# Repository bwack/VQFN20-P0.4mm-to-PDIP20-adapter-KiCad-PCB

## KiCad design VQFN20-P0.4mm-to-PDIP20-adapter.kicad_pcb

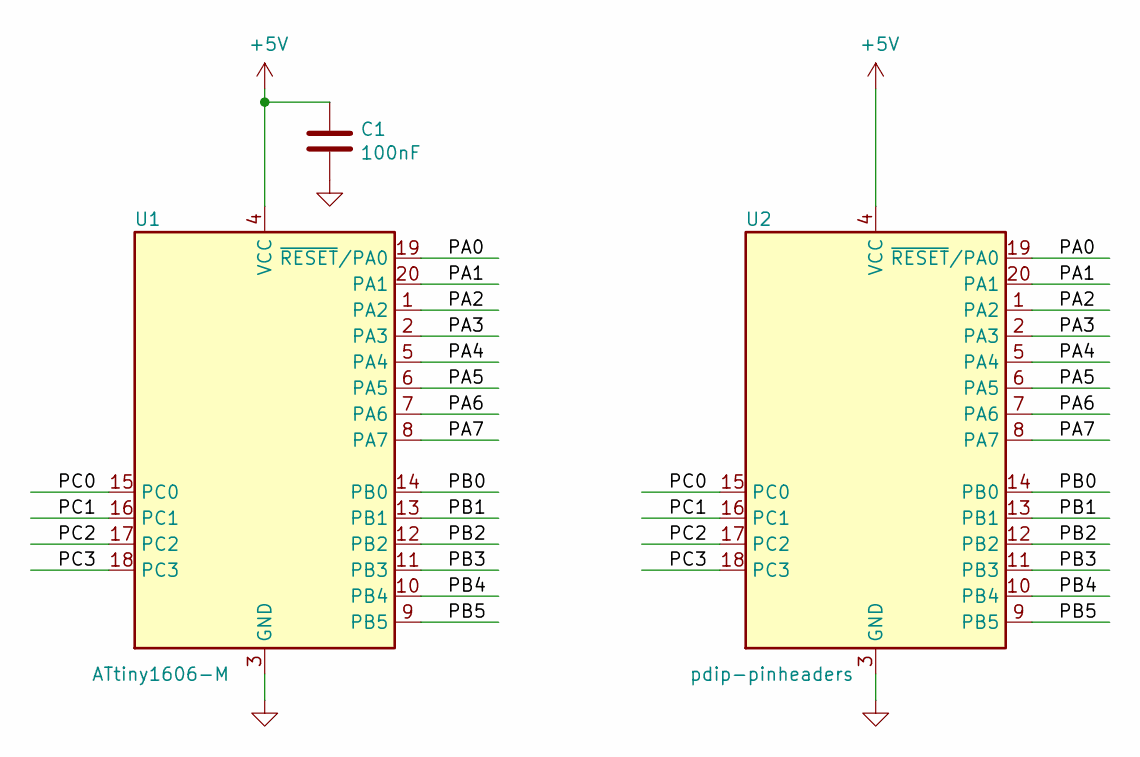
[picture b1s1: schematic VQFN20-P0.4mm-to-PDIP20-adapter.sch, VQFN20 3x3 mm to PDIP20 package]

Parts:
C1: 100nF; C_0603_1608Metric_Pad1.05x0.95mm_HandSolder
U1: ATtiny1606-M; VQFN-20-1EP_3x3mm_P0.4mm_EP1.7x1.7mm
U2: pdip-pinheaders; DIP-20_W7.62mm

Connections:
+5V: C1.1, U1.4 (VCC), U2.4 (VCC)
/PA0: U1.19 (~RESET~/PA0), U2.19 (~RESET~/PA0)
/PA1: U1.20 (PA1), U2.20 (PA1)
/PA2: U1.1 (PA2), U2.1 (PA2)
/PA3: U1.2 (PA3), U2.2 (PA3)
/PA4: U1.5 (PA4), U2.5 (PA4)
/PA5: U1.6 (PA5), U2.6 (PA5)
/PA6: U1.7 (PA6), U2.7 (PA6)
/PA7: U1.8 (PA7), U2.8 (PA7)
/PB0: U1.14 (PB0), U2.14 (PB0)
/PB1: U1.13 (PB1), U2.13 (PB1)
/PB2: U1.12 (PB2), U2.12 (PB2)
/PB3: U1.11 (PB3), U2.11 (PB3)
/PB4: U1.10 (PB4), U2.10 (PB4)
/PB5: U1.9 (PB5), U2.9 (PB5)
/PC0: U1.15 (PC0), U2.15 (PC0)
/PC1: U1.16 (PC1), U2.16 (PC1)
/PC2: U1.17 (PC2), U2.17 (PC2)
/PC3: U1.18 (PC3), U2.18 (PC3)
GND: C1.2, U1.3 (GND), U1.21 (GND), U2.3 (GND), U2.21 (GND)

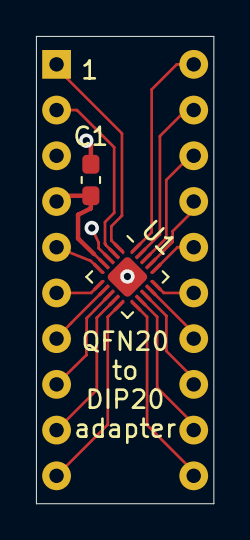
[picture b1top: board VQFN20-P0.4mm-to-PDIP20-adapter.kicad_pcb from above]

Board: 2 copper layers, 9.9 x 26.0 mm, 3 parts (0 on the bottom side), 20 nets.

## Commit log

2020-11-03 readme update
